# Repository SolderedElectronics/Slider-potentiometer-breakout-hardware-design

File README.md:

# Slider potentiometer breakout Hardware Design

## About the Product

|  |
| :----------------------------------------------------------: |
| [Buy Slider potentiometer breakout](https://www.solde.red/333130) |

Potentiometers are well known all around, and the sliding potentiometer is just one of its versions.You’ve probably seen it in some music equipment, and now you have the chance to add it to your project!

---

## Repository Contents

This repository contains all design files for Slider potentiometer breakout, organized as follows:

- **`CAD` folder**: Contains KiCAD design files, including:
  - Schematics
  - PCB layout
  - Panel PCB layout
  - Source 3D files in Fusion360, if any
  - All files are sorted by version with a detailed change log.
- **`OUTPUTS` folder**: Includes all production-ready files, such as:
  - Bill of Materials (BOM) and interactive BOM (iBOM)
  - PDF versions of schematics
  - 3D `.step` file of the board
  - 3D-printable models
  - Gerber files for PCB manufacturing
  - Image of the pinout of the board
  - Product image
  - Compliance, legal and generic sales documents

Refer to the `Change Log` in the CAD folder for details about updates between versions.

---

## Learn More About the Product

Beyond the repository, explore the following resources:

### Soldered Verify

The **Soldered Verify** system ensures every board you purchase from Soldered is fully functional. It also provides access to exclusive test data for your product. To get started, find the unique Soldered Verify ID on your product's packaging and enter the ID on the [Soldered Verify page](https://soldered.com/verify/) to access test results and additional product details.

### Soldered Community

Soldered Community is your go-to place for technical support. Our engineers track and answer all questions posted there, and it’s a great space for the maker community. Get answers to your questions and solutions for your challenges at [Soldered Community](https://soldered.com/community).

### solde.red

solde.red is an ultimate URL shortener and information hub. Access it by typing solde.red/ followed by your product SKU, e.g., [solde.red/333000](https://solde.red/333000), to find getting-started guides, datasheets, open-source hardware and software files, certifications, images, pinouts, and more. Read more about the shortener [here](https://solde.red/info/).

---

## Contributing

Contributions are welcome! Here’s how you can get involved:

- Submit pull requests to enhance the design or fix issues.
- Report bugs or problems by opening an issue.

We encourage community collaboration to make this product even better.

---

## About Soldered

[Soldered for Makers](https://soldered.com) specializes in designing and manufacturing electronic products tailored for enthusiasts, ranging from hobbyists to professionals. Our portfolio includes electronic boards, sensors, and actuators that are widely utilized in fields such as microelectronics, mechatronics, robotics, programming, and IoT. Every product we offer is designed in-house and built upon open-source hardware and software platforms. Proudly certified and manufactured within the European Union, our catalog likely includes the product you need for your project.

We complement these products with comprehensive tutorials and manuals, product descriptions, schematics, programming codes, and project examples. Our round-the-clock [customer and technical support](https://soldered.com/community) is available for all our products, irrespective of the sales channel. Soldered’s success and services reflect our maker community’s unwavering [trust](https://www.trustpilot.com/review/soldered.com), for which we are deeply grateful. Join our community and create using Soldered products.

---

## License

All Soldered open-source hardware (OSH) is under The TAPR Open Hardware License. Read more in the LICENSE file located in this repository.

**Disclaimer:**

No warranty - all designs in this repository are distributed in the hope that they will be useful, but without any warranty. They are provided "AS IS", therefore without warranty of any kind, either expressed or implied. The entire quality and performance of what you do with the contents of this repository are your responsibility. In no event Soldered Electronics will be liable for your damages, or losses, including any general, special, incidental, or consequential damage arising out of the use or inability to use the contents of this repository. 

---

## Have fun!

Thank you for your support from your fellow makers at Soldered Electronics.

Happy Making!

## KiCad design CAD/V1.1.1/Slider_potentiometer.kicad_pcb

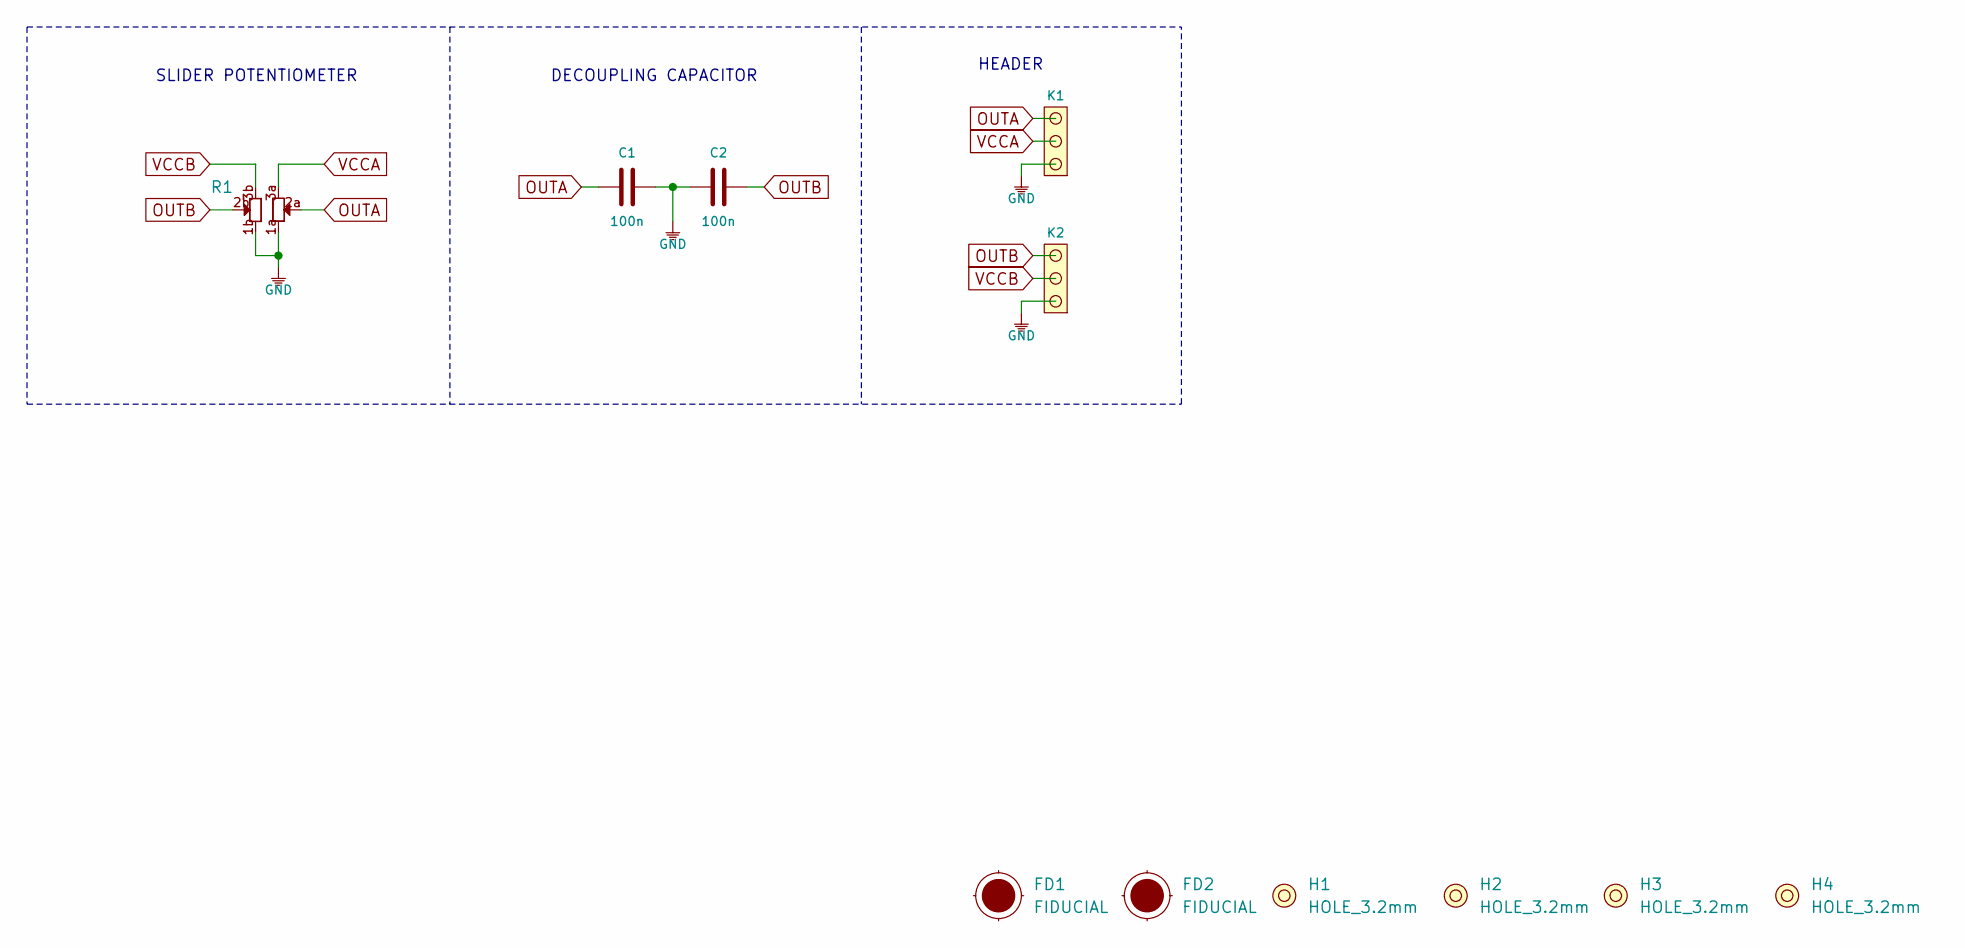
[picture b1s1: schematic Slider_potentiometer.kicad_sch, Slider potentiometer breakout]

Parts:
C1, C2: 100n; 0603C
FD1, FD2: FIDUCIAL; FIDUCIAL_23
H1, H2, H3, H4: HOLE_3.2mm
K1, K2: HEADER_MALE_3X1
R1: SLIDER_POT

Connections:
GND: C1.2, C2.1, K1.1, K2.1, R1.1a, R1.1b
OUTA: C1.1, K1.3, R1.2a
OUTB: C2.2, K2.3, R1.2b
VCCA: K1.2, R1.3a
VCCB: K2.2, R1.3b

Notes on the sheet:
DECOUPLING CAPACITOR
HEADER
SLIDER POTENTIOMETER

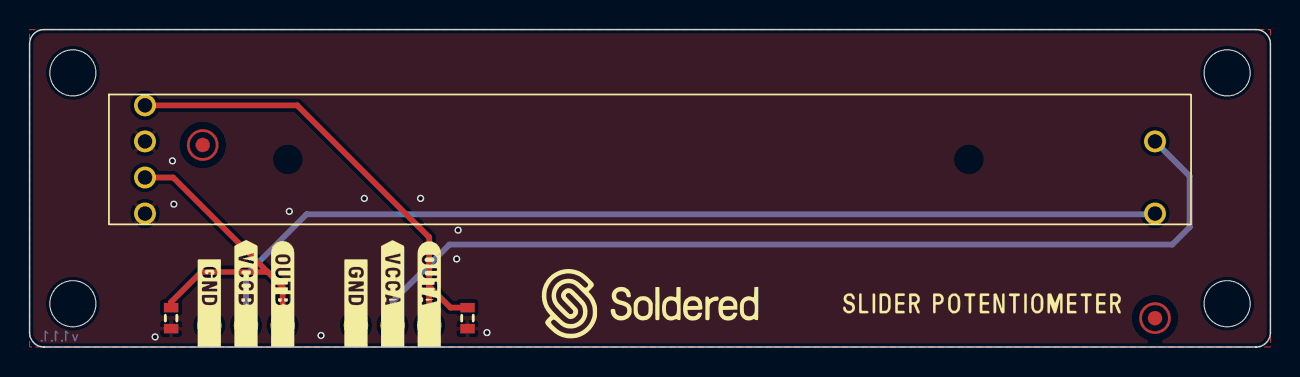
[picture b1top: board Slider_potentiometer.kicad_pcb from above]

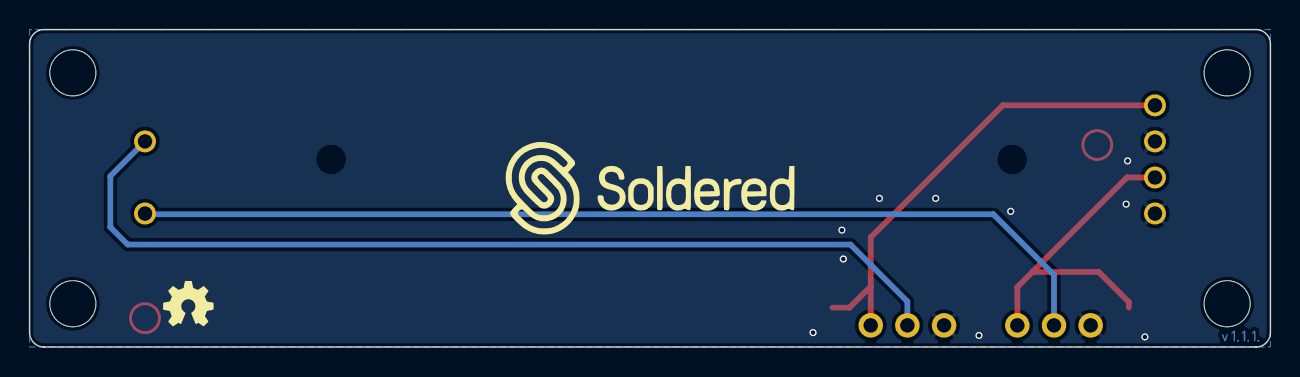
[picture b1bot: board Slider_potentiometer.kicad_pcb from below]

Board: 2 copper layers, 86.0 x 22.0 mm, 11 parts (2 on the bottom side), 5 nets.

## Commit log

2023-07-20 Updating open source files.
